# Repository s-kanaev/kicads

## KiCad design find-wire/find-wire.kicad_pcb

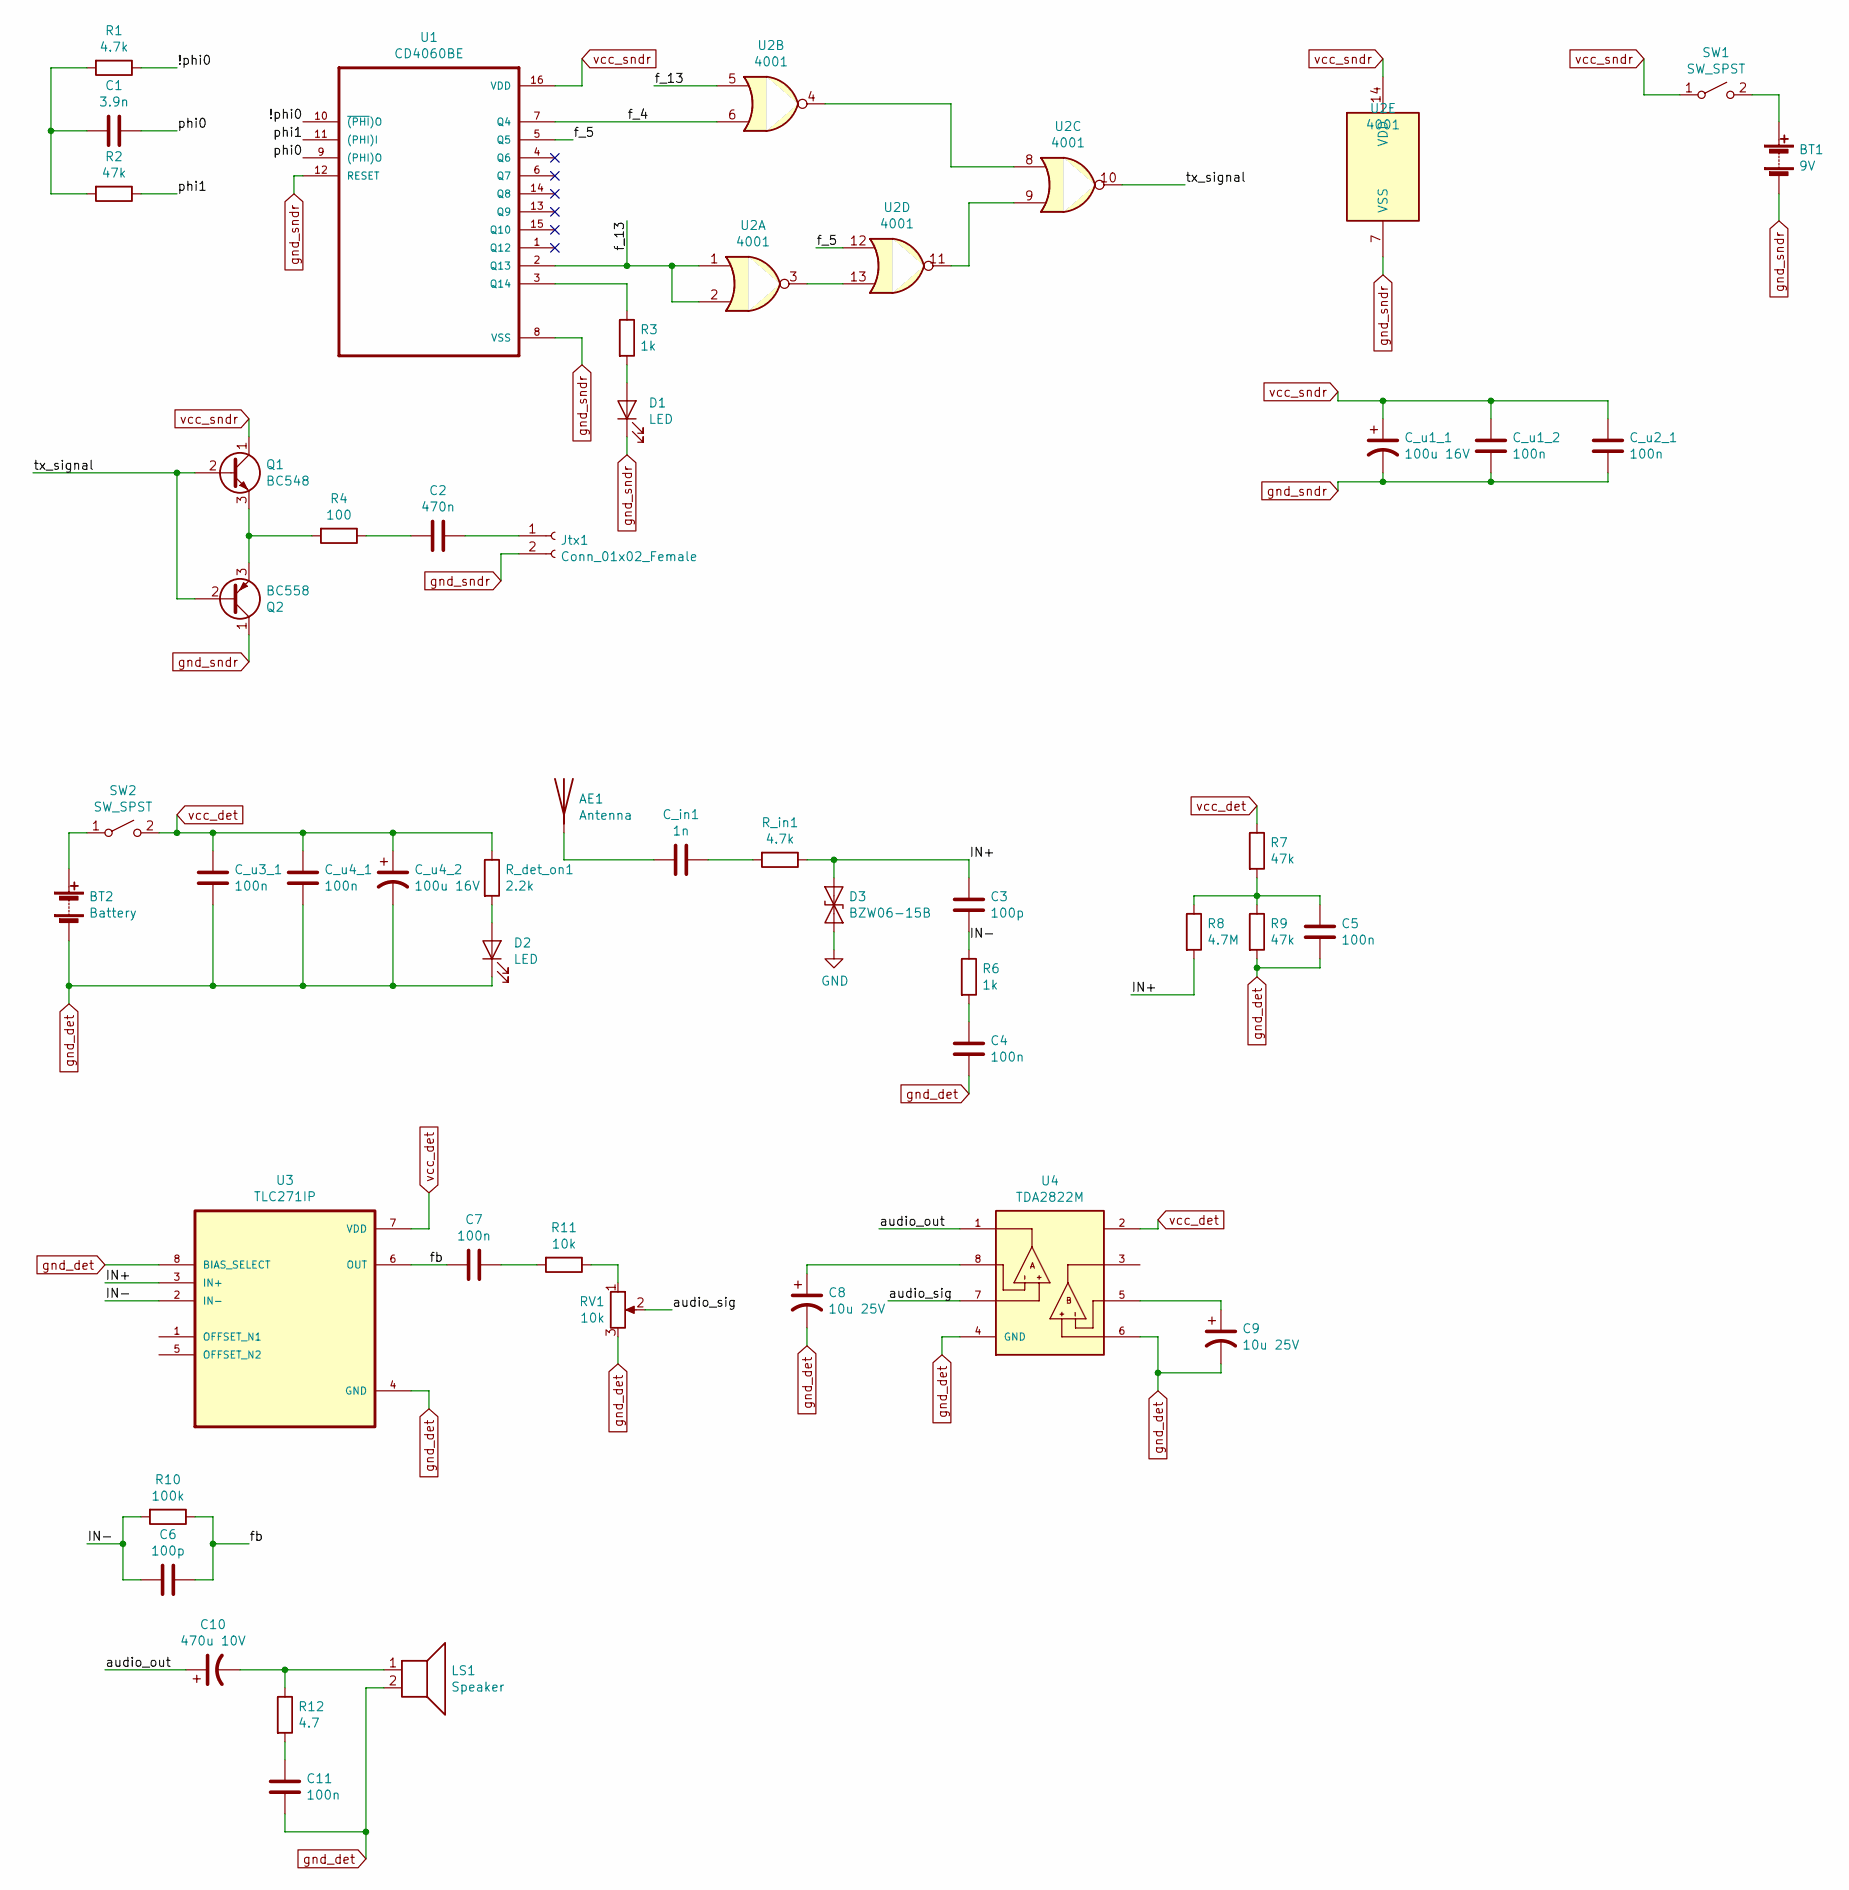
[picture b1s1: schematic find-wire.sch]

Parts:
AE1: Antenna; SolderWirePad_1x01_Drill2.5mm
BT1: 9V; SolderWirePad_1x02_P7.62mm_Drill2.5mm
BT2: Battery; SolderWirePad_1x02_P7.62mm_Drill2.5mm
C1: 3.9n; C_Disc_D10.0mm_W2.5mm_P5.00mm
C2: 470n; C_Disc_D10.0mm_W2.5mm_P5.00mm
C3, C6: 100p; C_Disc_D10.0mm_W2.5mm_P5.00mm
C4: 100n; C_Disc_D4.3mm_W1.9mm_P5.00mm
C5, C7, C11: 100n; C_Disc_D10.0mm_W2.5mm_P5.00mm
C8, C9: 10u 25V; CP_Radial_D8.0mm_P5.00mm
C10: 470u 10V; CP_Radial_D8.0mm_P2.50mm
C_in1: 1n; C_Disc_D10.0mm_W2.5mm_P5.00mm
C_u1_1, C_u4_2: 100u 16V; CP_Radial_D8.0mm_P2.50mm
C_u1_2, C_u2_1, C_u3_1, C_u4_1: 100n; C_Disc_D10.0mm_W2.5mm_P5.00mm
D1, D2: LED; LED_D3.0mm
D3: BZW06-15B; D_DO-15_P3.81mm_Vertical_AnodeUp
Jtx1: Conn_01x02_Female; SolderWirePad_1x02_P7.62mm_Drill2.5mm
LS1: Speaker; SolderWirePad_1x02_P7.62mm_Drill2.5mm
Q1: BC548; TO-92_HandSolder
Q2: BC558; TO-92_HandSolder
R1: 4.7k; R_Axial_DIN0207_L6.3mm_D2.5mm_P5.08mm_Vertical
R2, R7, R9: 47k; R_Axial_DIN0207_L6.3mm_D2.5mm_P5.08mm_Vertical
R3, R6: 1k; R_Axial_DIN0207_L6.3mm_D2.5mm_P5.08mm_Vertical
R4: 100; R_Axial_DIN0207_L6.3mm_D2.5mm_P5.08mm_Vertical
R8: 4.7M; R_Axial_DIN0207_L6.3mm_D2.5mm_P5.08mm_Vertical
R10: 100k; R_Axial_DIN0207_L6.3mm_D2.5mm_P5.08mm_Vertical
R11: 10k; R_Axial_DIN0207_L6.3mm_D2.5mm_P5.08mm_Vertical
R12: 4.7; R_Axial_DIN0207_L6.3mm_D2.5mm_P5.08mm_Vertical
RV1: 10k; SolderWirePad_1x03_P7.62mm_Drill2.5mm
R_det_on1: 2.2k; R_Axial_DIN0207_L6.3mm_D2.5mm_P5.08mm_Vertical
R_in1: 4.7k; R_Axial_DIN0207_L6.3mm_D2.5mm_P5.08mm_Vertical
SW1, SW2: SW_SPST; SolderWirePad_1x02_P7.62mm_Drill2.5mm
U1: CD4060BE; DIP794W45P254L1969H508Q16
U2: 4001; DIP-14_W7.62mm_Socket
U3: TLC271IP; DIP794W45P254L959H508Q8
U4: TDA2822M; DIP762W45P254L1092H508Q8; PARTREV September 2003

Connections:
/!phi0: R1.1, U1.10 (~(PHI)O~)
/IN+: C3.1, D3.1 (A1), R8.2, R_in1.1, U3.3 (IN+)
/IN-: C3.2, C6.2, R6.1, R10.2, U3.2 (IN-)
/audio_out: C10.1, U4.1
/audio_sig: RV1.2, U4.7
/f_4: U1.7 (Q4), U2.6
/f_5: U1.5 (Q5), U2.12
/f_13: U1.2 (Q13), U2.1, U2.2, U2.5
/fb: C6.1, C7.2, R10.1, U3.6 (OUT)
/phi0: C1.1, U1.9 ((PHI)O)
/phi1: R2.1, U1.11 ((PHI)I)
/tx_signal: Q1.2 (B), Q2.2 (B), U2.10
unnamed: AE1.1, C_in1.2
unnamed: BT1.1 (+), SW1.2 (B)
unnamed: BT2.1 (+), SW2.1 (A)
unnamed: C1.2, R1.2, R2.2
unnamed: C2.1, Jtx1.1
unnamed: C2.2, R4.1
unnamed: C4.1, R6.2
unnamed: C5.1, R7.2, R8.1, R9.1
unnamed: C7.1, R11.2
unnamed: C8.1, U4.8
unnamed: C9.1, U4.5
unnamed: C10.2, LS1.1, R12.1
unnamed: C11.1, R12.2
unnamed: C_in1.1, R_in1.2
unnamed: D1.2 (A), R3.2
unnamed: D2.2 (A), R_det_on1.2
unnamed: Q1.3 (E), Q2.3 (E), R4.2
unnamed: R3.1, U1.3 (Q14)
unnamed: R11.1, RV1.1
unnamed: U2.4, U2.8
unnamed: U2.9, U2.11
unnamed: U2.3, U2.13
gnd_det: BT2.2 (-), C4.2, C5.2, C8.2, C9.2, C11.2, C_u3_1.1, C_u4_1.2, C_u4_2.2, D2.1 (K), LS1.2, R9.2, RV1.3, U3.4 (GND), U3.8 (BIAS_SELECT), U4.4 (GND), U4.6
gnd_sndr: BT1.2 (-), C_u1_1.2, C_u1_2.2, C_u2_1.2, D1.1 (K), Jtx1.2, Q2.1 (C), U1.8 (VSS), U1.12 (RESET), U2.7 (VSS)
vcc_det: C_u3_1.2, C_u4_1.1, C_u4_2.1, R7.1, R_det_on1.1, SW2.2 (B), U3.7 (VDD), U4.2
vcc_sndr: C_u1_1.1, C_u1_2.1, C_u2_1.1, Q1.1 (C), SW1.1 (A), U1.16 (VDD), U2.14 (VDD)

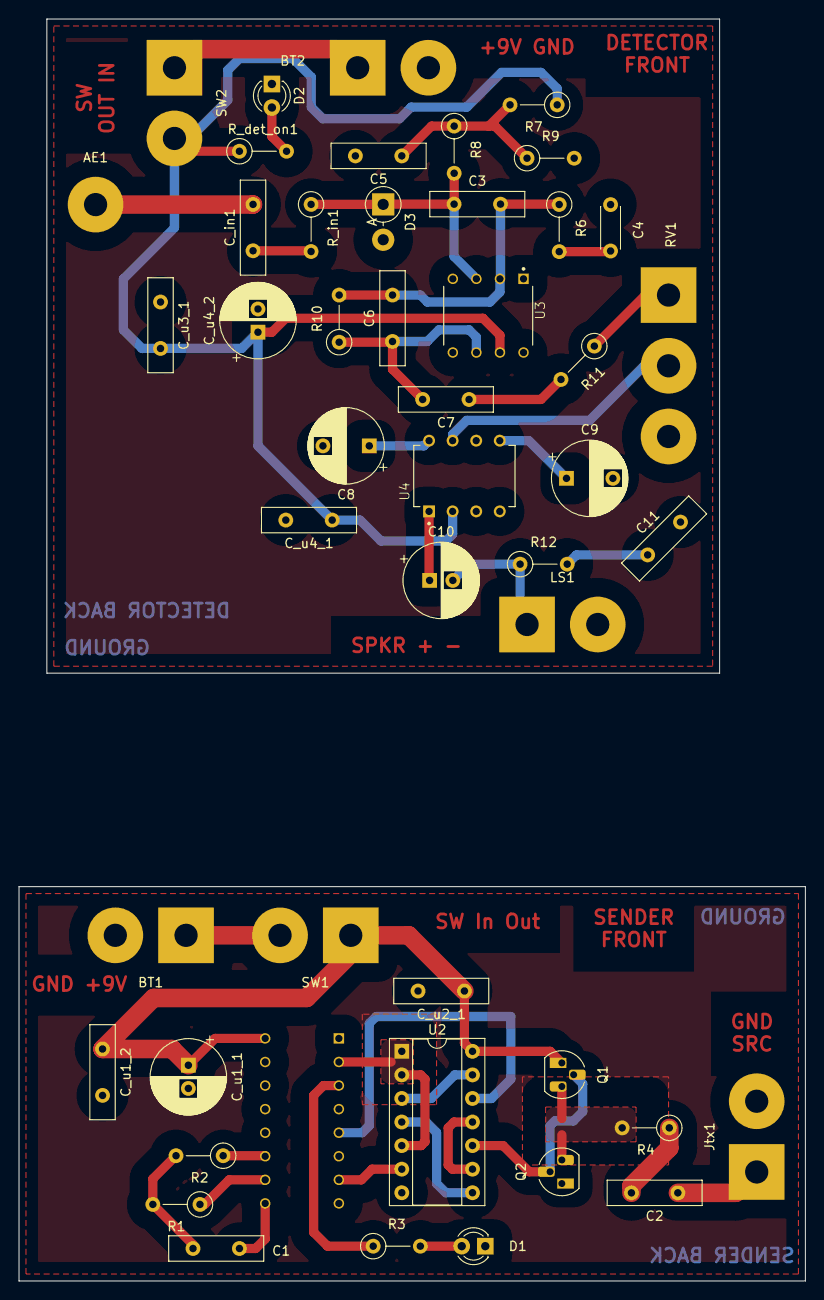
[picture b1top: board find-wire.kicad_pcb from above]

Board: 2 copper layers, 84.8 x 136.0 mm, 48 parts (1 on the bottom side), 38 nets.
